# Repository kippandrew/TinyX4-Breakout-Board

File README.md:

About
-----

The TinyX4 Breakout Board is designed to make developing with the Atmel ATTiny84 and ATTiny44 micro-controllers easier. 

Features
--------
- Onboard 5V regulator (maximum voltage 20V)
- Dedicated ICSP header
- Power indicator LED
- All pins broken out 

Parts List
-----
<table>
    <tr>
        <th>Part</th>
        <th>Description</th>
        <th>Part Number</th>
    </tr>
    <tr>
        <td>IC1</td>
        <td>Atmel ATTINY84-20PU</td>
        <td>DigiKey P/N: <a href="http://www.digikey.com/product-detail/en/ATTINY84-20PU/ATTINY84-20PU-ND/1245916">ATTINY84-20PU-ND</a></td>
    </tr>
    <tr>
        <td>IC1 (Alternate)</td>
        <td>DIP IC SOCKET 2x7</td>
        <td>DigiKey P/N: <a href="http://www.digikey.com/product-detail/en/1-390261-3/A100205-ND/1125623">A100205-ND</a></td>
    </tr>
    <tr>
        <td>IC2</td>
        <td>LM1117MP-5.0</td>
        <td>DigiKey P/N: <a href="http://www.digikey.com/product-detail/en/LM1117MP-5.0%2FNOPB/LM1117MP-5.0%2FNOPBTR-ND/363590">LM1117MP-5.0/NOPBTR-ND</a></td>
    </tr>
    <tr>
        <td>C1</td>
        <td>22uF 16V 1206 SMD</td>
        <td>DigiKey P/N: <a href="http://www.digikey.com/product-detail/en/EMK316BJ226ML-T/587-1433-1-ND/1004064">587-1433-1-ND</a></td>
    </tr>
    <tr>
        <td>C2</td>
        <td>0.1uF 16V 1206 SMD</td>
        <td>DigiKey P/N: <a href="http://www.digikey.com/product-detail/en/C1206C104K4RACTU/399-9305-1-ND/3522823">399-9305-1-ND</a></td>
    </tr>
    <tr>
        <td>C3</td>
        <td>10uF 16V 1206 SMD</td>
        <td>DigiKey P/N: <a href="http://www.digikey.com/product-detail/en/EMK316F106ZL-T/587-1354-1-ND/931131">587-1354-1-ND</a></td>
    </tr>
    <tr>
        <td>R1</td>
        <td>220 Ohm 1206 SMD 1/4W</td>
        <td>DigiKey P/N: <a href="http://www.digikey.com/product-detail/en/RC1206JR-07220RL/311-220ERCT-ND/732198">311-220ERCT-ND</a></td>
    </tr>
    <tr>
        <td>R2</td>
        <td>240 Ohm 1206 SMD 1/4W</td>
        <td>DigiKey P/N: <a href="http://www.digikey.com/product-detail/en/RC1206JR-07240RL/311-240ERCT-ND/732202">311-240ERCT-ND</a></td>
    </tr>
    <tr>
        <td>R3</td>
        <td>720 Ohm 1206 SMD 1/4W</td>
        <td>DigiKey P/N: <a href="http://www.digikey.com/product-detail/en/RC1206JR-07750RL/311-750ERCT-ND/732282">311-750ERCT-ND</a></td>
    </tr>
    <tr>
        <td>D1</td>
        <td>DIODE 100V 250mA SOD323</td>
        <td>DigiKey P/N: <a href="http://www.digikey.com/product-detail/en/BAS316,115/568-5003-1-ND/2209919">568-5003-1-ND</a></td>
    </tr>
    <tr>
        <td>LED1</td>
        <td>LED Red 1206 SMD</td>
        <td>DigiKey P/N: <a href="http://www.digikey.com/product-detail/en/LTST-C150CKT/160-1167-1-ND/269239">160-1167-1-ND</a></td>
    </tr>
    <tr>
        <td>ISCP Header</td>
        <td>0.1" Pitch Header Male 2x3</td>
        <td>DigiKey P/N: <a href="http://www.digikey.com/product-detail/en/77313-422R06LF/609-4517-ND/2665635">609-4517-ND</a></td>
    </tr>
    <tr>
        <td>J1, J2</td>
        <td>0.1" Pitch Header Female 1x8</td>
        <td><a href="http://www.digikey.com/product-detail/en/66951-008LF/609-2238-ND/1002553">609-2238-ND</a></td>
    </tr>
</table>

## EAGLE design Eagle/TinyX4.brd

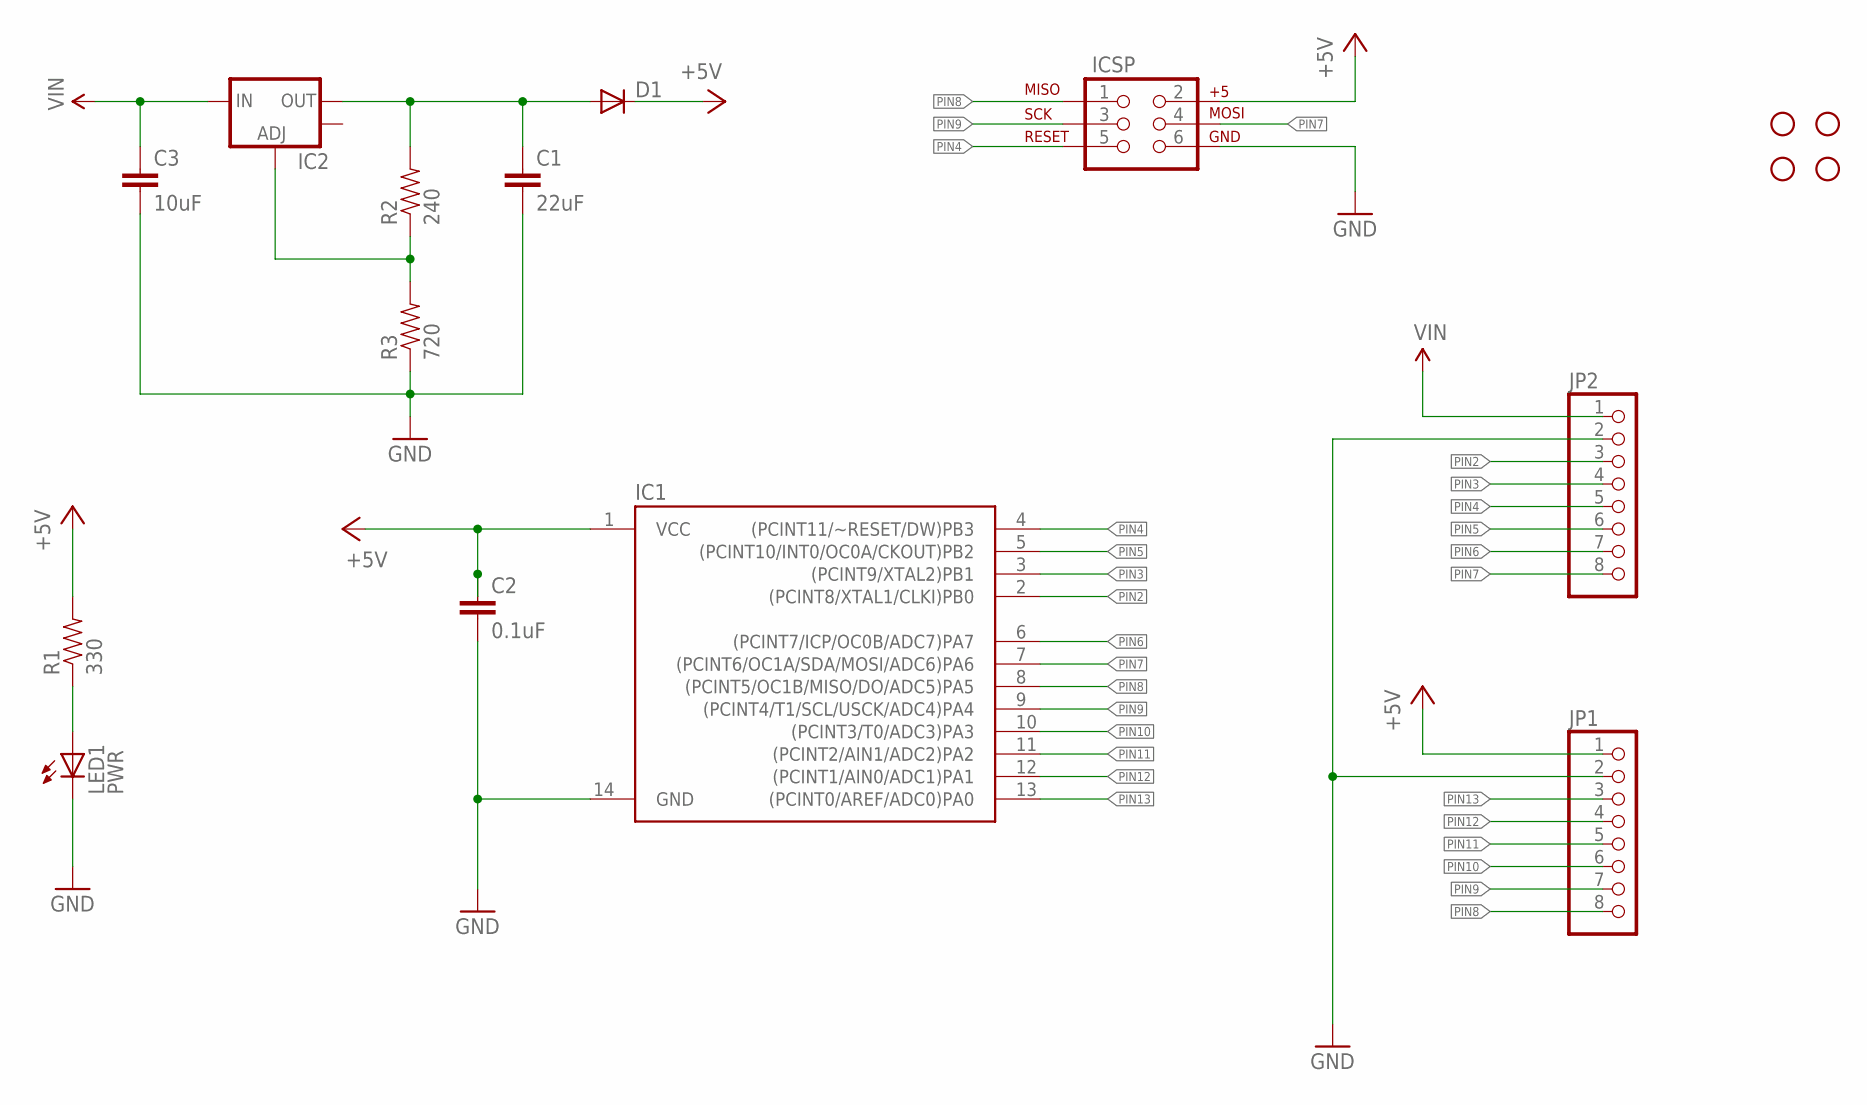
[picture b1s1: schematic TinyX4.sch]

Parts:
C1: 22uF; 1206
C2: 0.1uF; 1206
C3: 10uF; 1206
D1: DIODESOD; SOD-323
IC1: ATTINY84ATTINY84-20PU; DIL14
IC2: V_REG_LM1117SOT223; SOT223
ICSP: AVR_SPI_PRG_6PTH; 2X3
JP1, JP2: PINHD-1X8; 1X08
LED1: PWR; LED-1206
R1: 330; 1206
R2: 240; 1206
R3: 720; 1206
STANDOFF1, STANDOFF2, STANDOFF3, STANDOFF4: STAND-OFFTIGHT; STAND-OFF-TIGHT

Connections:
+5V: C2.1, D1.1 (C), IC1.1 (VCC), ICSP.2, JP1.1, R1.2
GND: C1.2, C2.2, C3.2, IC1.14 (GND), ICSP.6, JP1.2, JP2.2, LED1.C, R3.1
unnamed: LED1.A, R1.1
unnamed: C1.1, D1.2 (A), IC2.2 (OUT), R2.2
unnamed: IC2.1 (ADJ), R2.1, R3.2
PIN2: IC1.2 ((PCINT8/XTAL1/CLKI)PB0), JP2.3
PIN3: IC1.3 ((PCINT9/XTAL2)PB1), JP2.4
PIN4: IC1.4 ((PCINT11/~RESET/DW)PB3), ICSP.5, JP2.5
PIN5: IC1.5 ((PCINT10/INT0/OC0A/CKOUT)PB2), JP2.6
PIN6: IC1.6 ((PCINT7/ICP/OC0B/ADC7)PA7), JP2.7
PIN7: IC1.7 ((PCINT6/OC1A/SDA/MOSI/ADC6)PA6), ICSP.4, JP2.8
PIN8: IC1.8 ((PCINT5/OC1B/MISO/DO/ADC5)PA5), ICSP.1, JP1.8
PIN9: IC1.9 ((PCINT4/T1/SCL/USCK/ADC4)PA4), ICSP.3, JP1.7
PIN10: IC1.10 ((PCINT3/T0/ADC3)PA3), JP1.6
PIN11: IC1.11 ((PCINT2/AIN1/ADC2)PA2), JP1.5
PIN12: IC1.12 ((PCINT1/AIN0/ADC1)PA1), JP1.4
PIN13: IC1.13 ((PCINT0/AREF/ADC0)PA0), JP1.3
VIN: C3.1, IC2.3 (IN), JP2.1

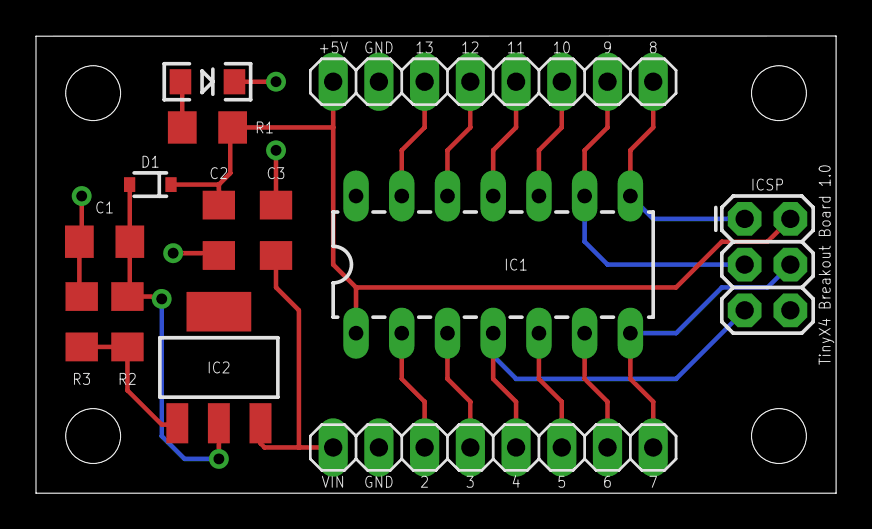
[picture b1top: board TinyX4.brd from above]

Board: 2 copper layers, 44.5 x 25.4 mm, 17 parts (0 on the bottom side), 18 nets.

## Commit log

2013-02-06 added gebers, updated readme
2013-02-17 added images

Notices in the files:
Eagle/TinyX4.brd:
(c) 2013 Andy Kipp
parts and their libraries:
SparkFun-DigitalIC: Licensing: CC v3.0 Share-Alike You are welcome to use this library for commercial purposes.
